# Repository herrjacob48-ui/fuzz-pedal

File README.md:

# BJT Fuzz Guitar Pedal

A single-transistor fuzz pedal with diode clipping, designed in KiCad. I prototyped the circuit on a breadboard and tested it with a digital oscilloscope, then captured the schematic and a 2-layer PCB layout and simulated the design in ngspice.

**Status:** Breadboard prototype built and tested. The PCB is designed and passes DRC, but it has **not been fabricated yet**.

## Overview

| | |
|---|---|
| Topology | Common-emitter NPN gain stage (MPSA42) with back-to-back 1N4148 clipping |
| Supply | 9V DC |
| Controls | FUZZ (10k, variable emitter resistance), VOLUME (100k) |
| Tools | KiCad 10 (schematic, PCB, ngspice), digital oscilloscope |
| Board | 2-layer PCB with pin headers for off-board jacks, pots, and battery |

## How it works

1. **Input:** a 1M pull-down sets the input DC level. C_IN1 (4.7µF) and R_IN1 (33k) couple the guitar signal to the transistor base.
2. **Gain stage:** Q1 is biased by a 1M / 100k divider (R_B1 / R_B2), with R_C1 (8.2k) as the collector load. C_E1 (10µF) bypasses the emitter for audio, so the FUZZ pot (RV1) mainly acts as an adjustable DC emitter resistance that shifts the bias point.
3. **Clipping:** C_OUT1 couples the collector signal to a pair of antiparallel 1N4148 diodes, which flatten the waveform into a near-square wave.
4. **Output:** RV2 (100k) sets the output level.

Full schematic: [`docs/fuzz_pedal_schematic_cropped.pdf`](docs/fuzz_pedal_schematic_cropped.pdf)

## Design values

| Ref | Value | Ref | Value |
|---|---|---|---|
| R_B1 | 1M | C_IN1 | 4.7µF |
| R_B2 | 100k | C_OUT1 | 4.7µF |
| R_C1 | 8.2k | C_E1 | 10µF |
| R_E1 | 100Ω | C_V1 | 47µF |
| R_IN1 | 33k | D1, D2 | 1N4148 |
| R_PULL1, R_PULL2 | 1M | Q1 | MPSA42 |
| RV1 (fuzz) | 10k | RV2 (volume) | 100k |

> These are the **design values**. The breadboard prototype was tuned by ear and its exact component values were not recorded. The schematic uses standard E-series values, with some values adjusted from the prototype.

## Simulation (ngspice in KiCad)

The simulation schematic is in [`simulation/`](simulation/). Device models are generic approximations (the transistor is a generic NPN with BF=100, not the manufacturer's MPSA42 model), so the results are approximate.

**DC operating point (RV1 branch set to 1k):**

| Node | Voltage |
|---|---|
| Base | 0.72 V |
| Emitter | 0.13 V |
| Collector | 8.07 V |
| Collector current | about 113 µA |

The transistor is in its active region with a low bias current. The collector sits close to the supply, which leaves little headroom for upward swing, so the stage clips asymmetrically before the diodes come into play.

**Transient response, 1 kHz sine input:**

At 200 mV the diode pair flattens the output into a roughly symmetric, square wave. The clipping level depends on the diode model, so the shape is not precise as to what the actual fabrication would produce.

The 20 mV run is included for comparison, showing how the response changes with input level.

## Breadboard prototype

The circuit was built and tested on a breadboard, and the oscilloscope photo shows the early prototyping/testing of the gain stage.

**Audio demo:** [`docs/pedal-demo.mp3`](docs/pedal-demo.mp3), recorded from the final breadboard prototype.

## PCB

- 2 layer board with a ground pour
- Passes DRC with zero errors and zero unrouted nets
- Through hole parts and pin headers, so it can be assembled by hand
- Not yet fabricated

## Repository layout

```
fuzz-pedal/
├── README.md
├── LICENSE
├── hardware/       KiCad project files (schematic and PCB layout)
├── simulation/     Simulation schematic and ngspice plots
├── docs/           Schematic PDF and audio demo
└── images/         PCB renders, breadboard and scope photos
```

## Lessons learned

- Simulating the design showed a low bias point (collector near the supply rail), which I would not have caught from the schematic alone.
- SPICE decides component type from the first letter of the reference designator, and a transistor model's pin order has to be mapped explicitly. A reversed collector/emitter assignment still runs without errors, and I caught it by checking the sign of the collector current.
- prototyping and wiring takes careful detail and patience, on several occasions I would quickly rewire the prototype, only to find several mistakes. Only until
I slowed down and paid attention was I able to fabricate a working prototype.

## Next steps

- Order the boards, assemble the PCB, and compare measured bias voltages with the simulation.
- Re-center the bias point and compare the waveform and sound.
- Run the simulation across the full range of the fuzz pot.
- Add reverse polarity protection on the 9V input and design for a 1590B enclosure.

## Author

Jacob Herr

## License

See [LICENSE](LICENSE).

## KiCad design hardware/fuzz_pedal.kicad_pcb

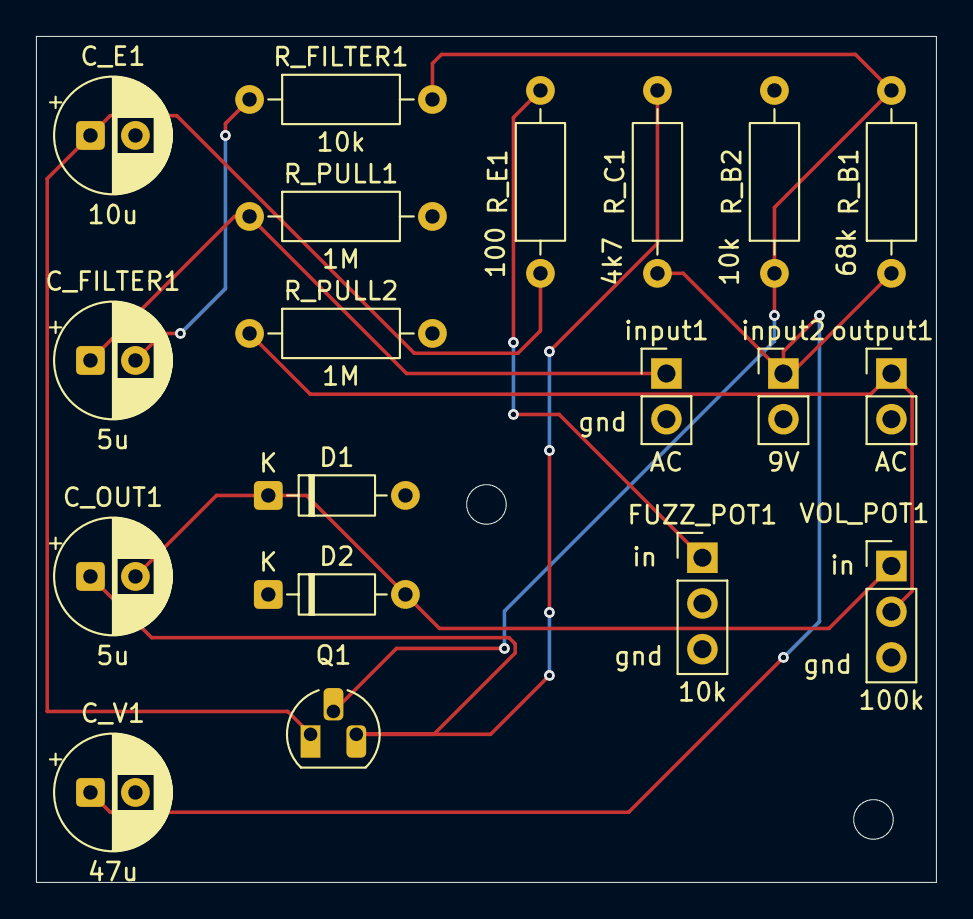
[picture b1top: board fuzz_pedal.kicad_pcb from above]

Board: 2 copper layers, 50.0 x 47.0 mm, 19 parts (0 on the bottom side), 10 nets.

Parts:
C_E1: 10u; CP_Radial_D6.3mm_P2.50mm
C_FILTER1: 5u; CP_Radial_D6.3mm_P2.50mm
C_OUT1: 5u; CP_Radial_D6.3mm_P2.50mm
C_V1: 47u; CP_Radial_D6.3mm_P2.50mm
D1, D2: 1N4148; D_DO-35_SOD27_P7.62mm_Horizontal
FUZZ_POT1: 10k; PinHeader_1x03_P2.54mm_Vertical
Q1: MPSA42; TO-92_HandSolder
R_B1: 68k; R_Axial_DIN0207_L6.3mm_D2.5mm_P10.16mm_Horizontal
R_B2: 10k; R_Axial_DIN0207_L6.3mm_D2.5mm_P10.16mm_Horizontal
R_C1: 4k7; R_Axial_DIN0207_L6.3mm_D2.5mm_P10.16mm_Horizontal
R_E1: 100; R_Axial_DIN0207_L6.3mm_D2.5mm_P10.16mm_Horizontal
R_FILTER1: 10k; R_Axial_DIN0207_L6.3mm_D2.5mm_P10.16mm_Horizontal
R_PULL1, R_PULL2: 1M; R_Axial_DIN0207_L6.3mm_D2.5mm_P10.16mm_Horizontal
VOL_POT1: 100k; PinHeader_1x03_P2.54mm_Vertical
input1: AC; PinHeader_1x02_P2.54mm_Vertical
input2: 9V; PinHeader_1x02_P2.54mm_Vertical
output1: AC; PinHeader_1x02_P2.54mm_Vertical

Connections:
/9V: C_V1.1, R_B1.1, R_C1.1, input2.1
GND: C_E1.2, C_V1.2, D1.2 (A), D2.1 (K), FUZZ_POT1.2, FUZZ_POT1.3, R_B2.2, R_PULL1.2, R_PULL2.2, VOL_POT1.3, input1.2, input2.2, output1.2
unnamed: C_FILTER1.2, R_FILTER1.1
unnamed: C_OUT1.2, D1.1 (K), D2.2 (A), VOL_POT1.1
unnamed: FUZZ_POT1.1, R_E1.2
unnamed: Q1.2 (B), R_B1.2, R_B2.1, R_FILTER1.2
unnamed: C_OUT1.1, Q1.3 (C), R_C1.2
unnamed: C_E1.1, Q1.1 (E), R_E1.1
unnamed: R_PULL2.1, VOL_POT1.2, output1.1
unnamed: C_FILTER1.1, R_PULL1.1, input1.1
